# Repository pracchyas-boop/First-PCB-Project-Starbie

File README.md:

# First-PCB-Project-Starbie
For Hack Club's event "Half Life", I started out by making my own version of the PCB for Starbie, changing several details of the template provided along the way.

Starbie is a Tamagotchi-like toy, containing a pet which has several reactions to the environment and how you interact with it, and has stats such as energy which change over time as you interact with it. The basic design we were given looks like this:

However, MY end product will look like this:

In order to create the Starbie, you will need KiCad and Arduino IDE.

Firstly, download [this Week 1 care package](https://github.com/SharKingStudios/Starbie/raw/refs/heads/main/Week%201%20Care%20Package.zip) and unzip it. Then open KiCad. Go to preferences, and then import the .sym files into the symbol library, and the .pretty files into the footprint library. These can be configured in KiCad's preferences.

Now open the schematic editor. By clicking a, you can import components. 

The components you need to import are:
- XIAO-ESP32-C3-SMD
- DHT11
- R1 R (basic resistor)
- Conn_01x08_Pin
- Conn_01x04_Pin
- SW_Push (x2)

Next you will need to assign footprints to these components

Change ALL of the components' assigned footprints such that they are assigned as this:

Then save and leave the schematic editor, go to PCB editor, and click this:

Now all your schematics should be laid out in PCB editor now. I recommend you route the by clicking l. Click any golden pad which has a blue line connecting it to another, and the screen should dim and show you where to go.

Now use "draw polygons" to create an outline for the PCB. This is the grey area in the above image of my PCB. Make any shape you want.

Now you want to add art. Save your project, and open Image Converter

Now download art you want to put on your PCB. Either make it yourself via another application, or download it online. After doing that, go back to Image converter and click "load source image" and export the art. Determine the output size, ensure the file is .kicad_mod, and is silkscreen (I may have amde a mistake where I made it copper and had to fix it. Oops!)

Put these images into a folder (that you make) called Images, placed inside the Week 1 care package folder. Import it into the footprint library. Now, click "place footprints" and find Images, then select your art.

And just put it onto your schematic. If you put the art close to the edge, you'll get a warning, but it's ignorable. To find warnings/errors, run DRC

This should be all you have: 

Now go to Arduino to make the firmware. The actual program is Firmware/Starbie/Starbie.ino. Keep the Starbie folder and the Starbie.ino file together; Arduino IDE expects the sketch file to be inside a folder with the same name.

Follow these directions (taken straight from the guide):

Install the current Arduino IDE.

Open File → Preferences. In Additional Boards Manager URLs, add:

https://espressif.github.io/arduino-esp32/package_esp32_index.json
Open Tools → Board → Boards Manager, search for esp32, and install esp32 by Espressif Systems.

Under Tools → Board → esp32, select XIAO_ESP32C3.

Open Sketch → Include Library → Manage Libraries. Install these libraries one at a time:

Adafruit GFX Library
Adafruit SSD1306
Adafruit MPU6050
DHT sensor library
If Arduino asks to install dependencies, choose Install All.
(end of these directions)

Now find "void drawHeart" in the code, and add this above it:

void drawSparkle(int x, int y) {
  display.drawPixel(x, y - 2, SSD1306_WHITE);
  display.drawPixel(x - 1, y - 1, SSD1306_WHITE);
  display.drawPixel(x + 1, y - 1, SSD1306_WHITE);
  display.drawPixel(x - 2, y, SSD1306_WHITE);
  display.drawPixel(x, y, SSD1306_WHITE);
  display.drawPixel(x + 2, y, SSD1306_WHITE);
  display.drawPixel(x - 1, y + 1, SSD1306_WHITE);
  display.drawPixel(x + 1, y + 1, SSD1306_WHITE);
  display.drawPixel(x, y + 2, SSD1306_WHITE);
}

Add this below display.drawBitmap()

if (!isNapping() && (now / 250) % 2 == 0) {
  drawSparkle(petX - 4, petY + 18);
}

Make a black and white 32x32 design for the sprite of your pet. Make a horizontal 1 bit per pixel output via image2cpp (website), and then find this in the code:
const uint8_t PROGMEM PET_SPRITE[] {
In the curly brackets, add the Arduino byte array you get from image2cpp.

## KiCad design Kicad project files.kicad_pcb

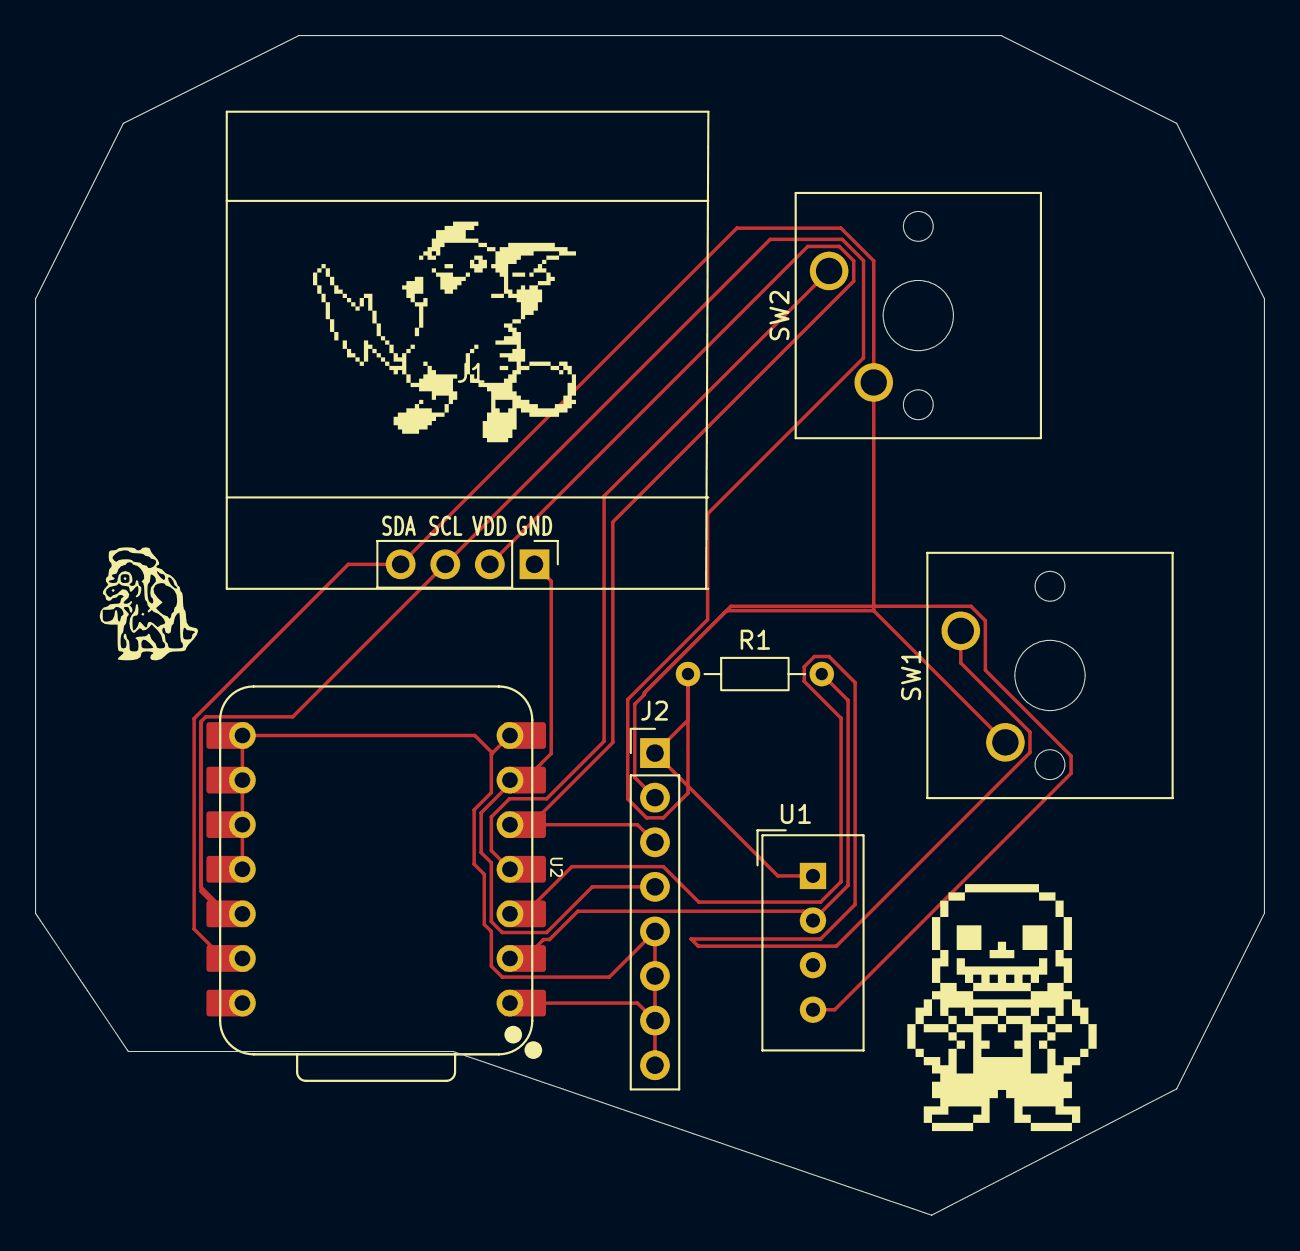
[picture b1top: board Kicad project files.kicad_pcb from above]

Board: 2 copper layers, 70.0 x 67.2 mm, 7 parts (0 on the bottom side), 8 nets.

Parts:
J1: Conn_01x04_Pin; Display_128x64_096_I2C
J2: Conn_01x08_Pin; PinHeader_1x08_P2.54mm_Vertical
R1: R; R_Axial_DIN0204_L3.6mm_D1.6mm_P7.62mm_Horizontal
SW1, SW2: SW_Push; SW_Cherry_MX_1.00u_PCB
U1: DHT11; Aosong_DHT11_5.5x12.0_P2.54mm
U2: XIAO-ESP32-C3-SMD; XIAO-ESP32-C6-DIP

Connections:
+3.3V: J1.3, J2.1, R1.1, U1.1 (VDD), U2.12 (3V3_OUT)
/DHT11 DATA: R1.2, U1.2 (DATA), U2.2 (D1)
/GPIO2: SW1.1, U2.3 (D2)
/GPIO3: SW2.1, U2.4 (D3)
/SCL: J1.2, J2.3, U2.5 (D4)
/SDA: J1.1, J2.4, U2.6 (D5)
/X: J2.5, J2.6, J2.7, J2.8, U2.1 (D0), U2.7 (D6), U2.8 (D7), U2.9 (D8), U2.10 (D9/BOOT), U2.11 (D10)
GND: J1.4, J2.2, SW1.2, SW2.2, U1.4 (GND), U2.13 (GND)
